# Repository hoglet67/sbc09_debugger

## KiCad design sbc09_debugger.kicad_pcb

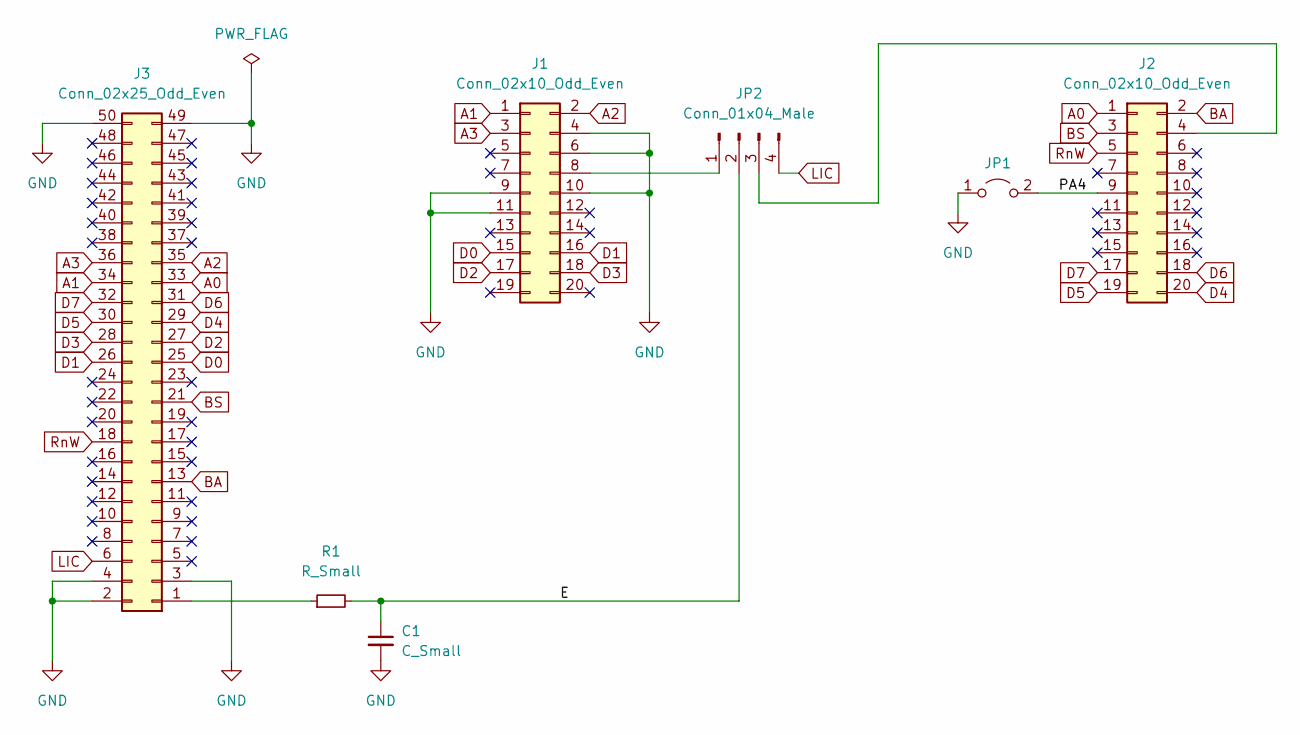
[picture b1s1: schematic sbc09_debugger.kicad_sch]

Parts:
C1: C_Small; C_Disc_D4.7mm_W2.5mm_P5.00mm
J1, J2: Conn_02x10_Odd_Even; PinSocket_2x10_P2.54mm_Vertical
J3: Conn_02x25_Odd_Even
JP1: Jumper_2_Open; PinHeader_1x02_P2.54mm_Vertical
JP2: Conn_01x04_Male; PinHeader_1x04_P2.54mm_Vertical
R1: R_Small; R_Axial_DIN0207_L6.3mm_D2.5mm_P10.16mm_Horizontal

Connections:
/E: C1.1, JP2.2, R1.2
/PA4: J2.9, JP1.2 (B)
A0: J2.1, J3.33
A1: J1.1, J3.34
A2: J1.2, J3.35
A3: J1.3, J3.36
BA: J2.2, J3.13
BS: J2.3, J3.21
D0: J1.15, J3.25
D1: J1.16, J3.26
D2: J1.17, J3.27
D3: J1.18, J3.28
D4: J2.20, J3.29
D5: J2.19, J3.30
D6: J2.18, J3.31
D7: J2.17, J3.32
GND: C1.2, J1.4, J1.6, J1.9, J1.10, J1.11, J3.2, J3.3, J3.4, J3.49, J3.50, JP1.1 (A)
LIC: J3.6, JP2.4
unnamed: J1.8, JP2.1
unnamed: J2.4, JP2.3
unnamed: J3.1, R1.1
RnW: J2.5, J3.18

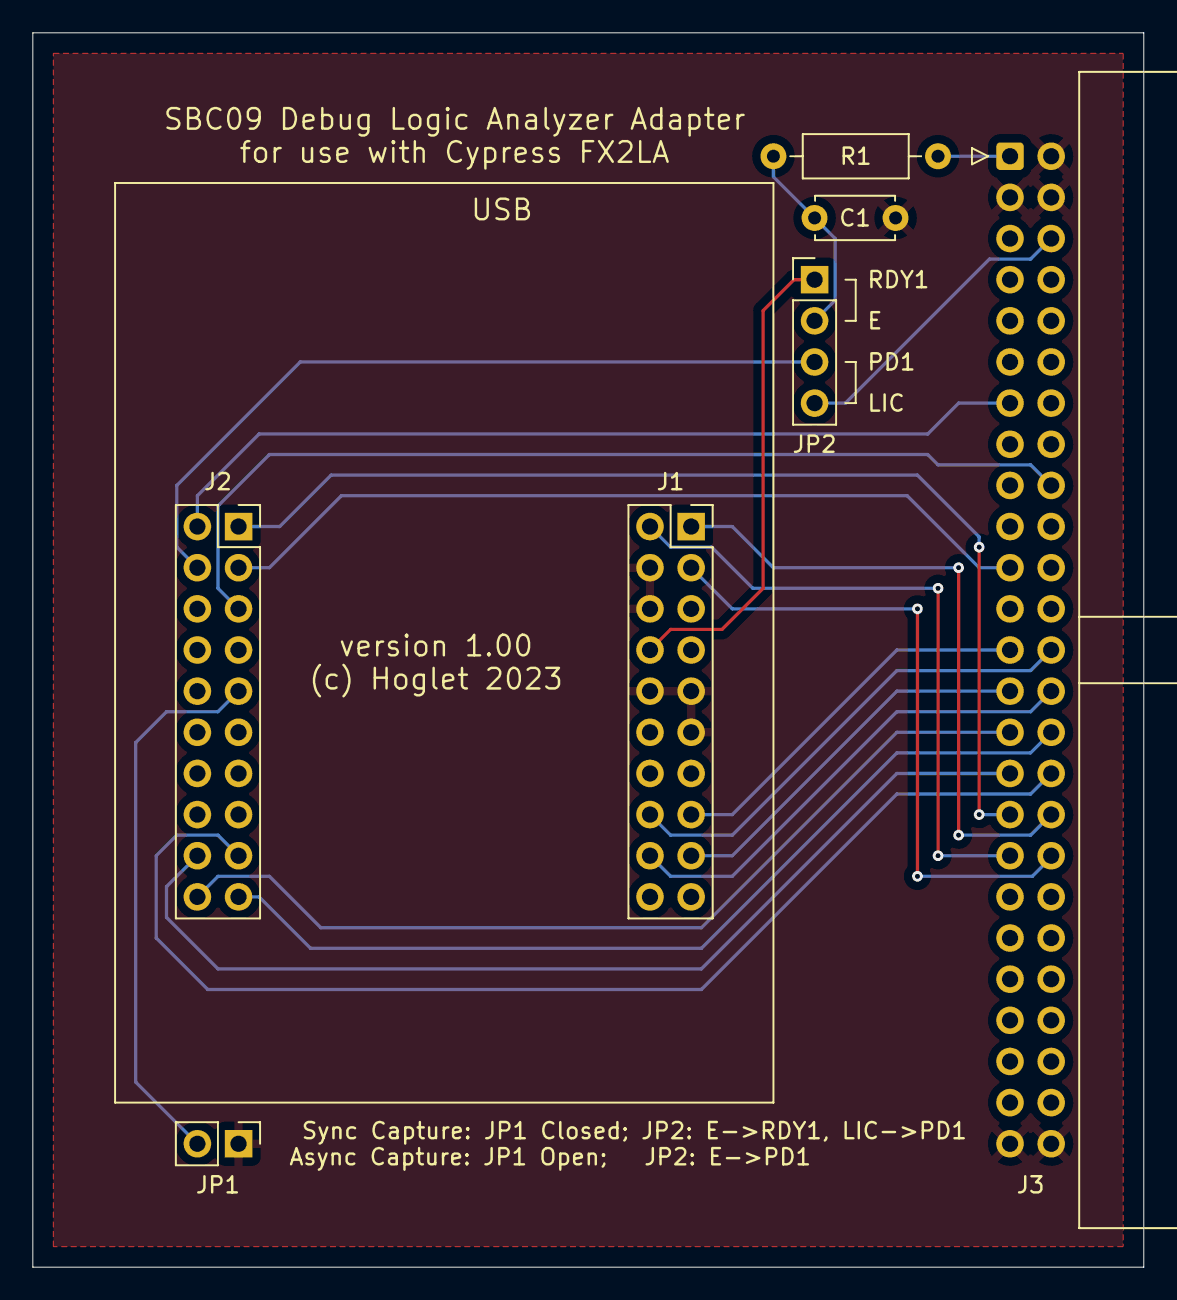
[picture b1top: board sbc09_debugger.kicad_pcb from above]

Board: 2 copper layers, 68.6 x 76.2 mm, 7 parts (0 on the bottom side), 22 nets.

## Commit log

2023-05-07 Initial version
2023-05-10 Use backplane pin numbering and the correct male IDC footprint
2023-06-14 Move R1/C1 slightly
2023-06-15 Added manufacturing files
2023-06-15 Added PDF schematic
